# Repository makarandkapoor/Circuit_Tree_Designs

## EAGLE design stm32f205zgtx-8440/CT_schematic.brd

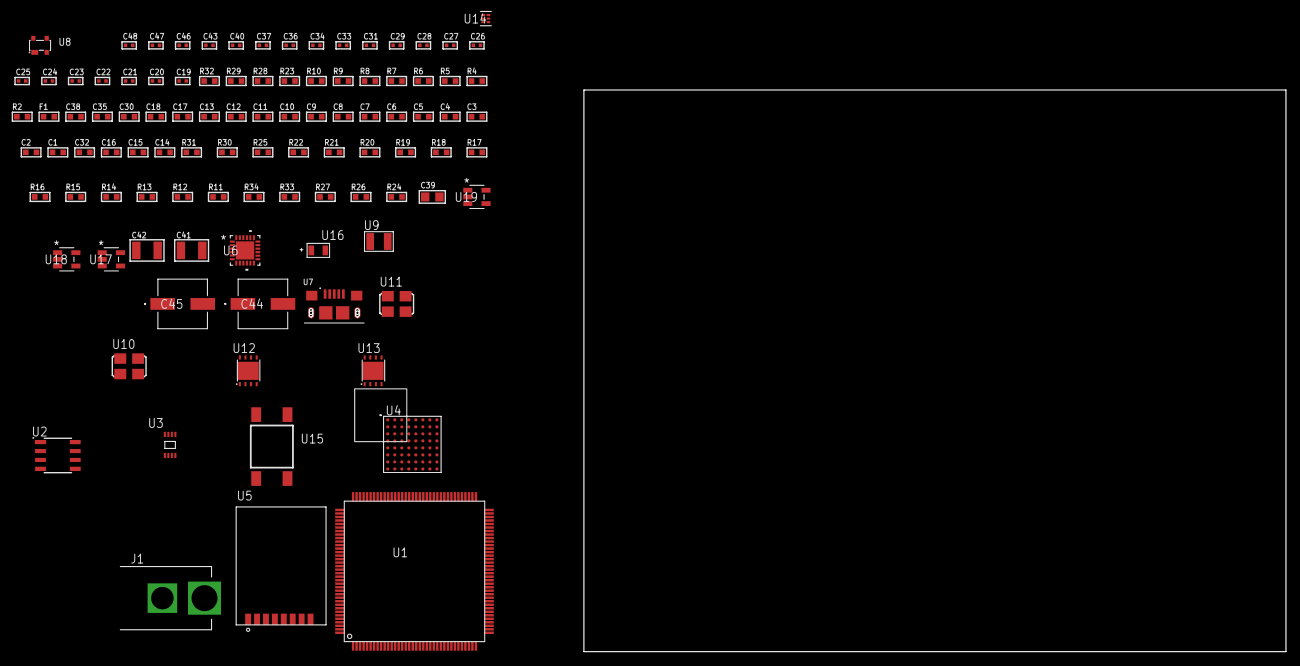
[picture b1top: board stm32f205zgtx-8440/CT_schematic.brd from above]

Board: 2 copper layers, 101 parts (0 on the bottom side), 104 nets, no tracks yet.

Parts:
C1, C18, C30, C35: 1e-06; C0603
C2, C3, C4, C5, C6, C7, C8, C9, C10, C11, C12, C13: 1e-07; C0603
C14: 4.7e-06; C0603
C15, C16, C32: 2.2e-06; C0603
C17: 1e-08; C0603
C19, C20: 1e-11; C0402
C21, C22, C24, C26, C28, C31, C33, C34, C36, C37, C40, C46, C47, C48: 1e-08; C0402
C23, C25, C27, C29, C43: 1e-07; C0402
C38: 8e-07; R0603
C39: 1e-05; C0805
C41, C42: 1e-05; C1210
C44, C45: 0.0001; EXV-9H
F1: 240.0; L0603
J1: PJ-037B; PJ-037B_PACKAGE
R2, R29: 1000.0; R0603
R4, R5, R6: 4700.0; R0603
R7, R8, R9, R10: 2200.0; R0603
R11, R12, R13, R14, R15, R16, R17, R18, R19, R20, R21, R22, R30, R31: 10000.0; R0603
R23: 8060.0; R0603
R24, R26, R27: 100000.0; R0603
R25: 36000.0; R0603
R28: 2231.0; R0603
R32: 9100.0; R0603
R33: 680000.0; R0603
R34: 120000.0; R0603
U1: STM32F205ZGT6; LQFP144
U2: AT24C02D-SSHM-T; AT24C02D
U3: 24AA00T-I/MNY; TDFN-8/6MM
U4: PC28F512P33BFD
U5: RFM75-S
U6: USB3317C-CP-TR; QFN-24
U7: 10118193-0001LF; FCI_10118193-0001LF
U8: prtr5v0u2ax; SOT143B
U9: ABS07-32.768KHZ-7-T
U10: ASFL1-25MHZ-NCS; ASFL1
U11: ASFL1-26MHZ-NCS; ASFL1
U12: LP2951ACSDX/NOPB; WSON-8
U13: LP3878SDX-ADJ/NOPB; WSON-8
U14: TPS3895ADRYR; SON-6
U15: 4-1437565-2; SW_4-1437565-2
U16: Q65110A2395; LGM67K-G1J2-24-Z
U17, U18, U19: nc7sz125m5x; NC7SZ125M5X

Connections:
CLK_CRYSTAL_U1_8: C19.1, U1.8, U9.1
CLK_CRYSTAL_U1_9: C20.1, U1.9, U9.2
CLK_U1_23: U1.23, U10.3
CLK_U6_23: U6.23, U11.3
GND: C1.2, C2.2, C3.2, C4.2, C5.2, C6.2, C7.2, C8.2, C9.2, C10.2, C11.2, C12.2, C13.2, C14.2, C15.2, C16.2, C17.2, C18.2, C19.2, C20.2, C21.2, C22.2, C23.2, C24.2, C25.2, C26.2, C27.2, C28.2, C29.2, C30.2, C31.2, C32.2, C33.2, C34.2, C35.2, C36.2, C37.2, C38.2, C39.2, C40.2, C41.2, C42.2, C43.2, C44.2, C45.2, C46.2, C47.2, C48.2, J1.2, R2.2, R11.2, R12.2, R14.2, R15.2, R23.2, R26.2, R29.2, R32.2, R34.2, U1.16, U1.31, U1.38, U1.51, U1.61, U1.83, U1.94, U1.107, U1.120, U1.130, U2.4, U3.4, U4.B2, U4.H2, U4.H4, U4.H6, U5.1, U6.25, U7.5, U7.6, U7.7, U7.8, U7.9, U8.1, U10.2, U11.2, U12.3, U12.4, U12.PAD, U13.3, U13.PAD, U14.2, U16.C, U17.1, U17.3, U18.1, U18.3, U19.1, U19.3
NET_U1_25: R5.1, U1.25, U18.4
NET_U1_33: C17.1, C18.1, F1.1, U1.32, U1.33
NET_U1_71: C15.1, U1.71
NET_U1_99: R10.1, U1.99, U2.5
NET_U1_100: R9.1, U1.100, U2.6
NET_U1_106: C16.1, U1.106
NET_U1_136: R7.1, U1.136, U3.6
NET_U1_138: R11.1, U1.138
NET_U1_140: R8.1, U1.140, U3.5
NET_U1_142: U15.3, U15.4
NET_U2_1: R13.1, U2.1
NET_U2_2: R14.1, U2.2
NET_U2_3: R15.1, U2.3
NET_U2_7: R12.1, U2.7
NET_U4_A4: C27.1, C28.1, U4.A4
NET_U4_C6: R19.1, U4.C6
NET_U4_D4: R4.1, U4.D4, U17.4
NET_U5_3: R21.1, U5.3
NET_U6_4: C32.1, U6.4
NET_U6_22: R6.1, U6.22, U19.4
NET_U6_24: R23.1, U6.24
NET_U7_1: C35.1, U6.2, U7.1, U8.4
NET_U7_2: U6.5, U7.2, U8.3
NET_U7_3: U6.6, U7.3, U8.2
NET_U12_5: R24.1, U12.5
NET_U12_7: R25.2, R26.1, U12.7
NET_U13_1: C40.1, U13.1
NET_U13_6: R28.2, R29.1, U13.6
NET_U13_8: R27.1, U13.8
NET_U14_1: R31.1, R32.1, U14.1
NET_U14_3: R33.2, R34.1, U14.3
NET_U14_4: R30.1, U14.4, U17.2, U18.2, U19.2
NET_U15_1: R2.1, U15.1, U15.2
PROC_FSMC_A0: U1.10, U4.A1
PROC_FSMC_A1: U1.11, U4.B1
PROC_FSMC_A2: U1.12, U4.C1
PROC_FSMC_A3: U1.13, U4.D1
PROC_FSMC_A4: U1.14, U4.D2
PROC_FSMC_A5: U1.15, U4.A2
PROC_FSMC_A6: U1.50, U4.C2
PROC_FSMC_A7: U1.53, U4.A3
PROC_FSMC_A8: U1.54, U4.B3
PROC_FSMC_A9: U1.55, U4.C3
PROC_FSMC_A10: U1.56, U4.D3
PROC_FSMC_A11: U1.57, U4.C4
PROC_FSMC_A12: U1.87, U4.A5
PROC_FSMC_A13: U1.88, U4.B5
PROC_FSMC_A14: U1.89, U4.C5
PROC_FSMC_A15: U1.90, U4.D7
PROC_FSMC_A16: U1.80, U4.D8
PROC_FSMC_A17: U1.81, U4.A7
PROC_FSMC_A18: U1.82, U4.B7
PROC_FSMC_A19: U1.2, U4.C7
PROC_FSMC_A20: U1.3, U4.C8
PROC_FSMC_A21: U1.4, U4.A8
PROC_FSMC_A22: U1.5, U4.G1
PROC_FSMC_A23: U1.1, U4.H8
PROC_FSMC_A24: U1.128, U4.B6
PROC_FSMC_CLK: U1.117, U4.E6
PROC_FSMC_D0: U1.85, U4.F2
PROC_FSMC_D1: U1.86, U4.E2
PROC_FSMC_D2: U1.114, U4.G3
PROC_FSMC_D3: U1.115, U4.E4
PROC_FSMC_D4: U1.58, U4.E5
PROC_FSMC_D5: U1.59, U4.G5
PROC_FSMC_D6: U1.60, U4.G6
PROC_FSMC_D7: U1.63, U4.H7
PROC_FSMC_D8: U1.64, U4.E1
PROC_FSMC_D9: U1.65, U4.E3
PROC_FSMC_D10: U1.66, U4.F3
PROC_FSMC_D11: U1.67, U4.F4
PROC_FSMC_D12: U1.68, U4.F5
PROC_FSMC_D13: U1.77, U4.H5
PROC_FSMC_D14: U1.78, U4.G7
PROC_FSMC_D15: U1.79, U4.E7
PROC_FSMC_NE1: R17.1, U1.123, U4.B4
PROC_FSMC_NL: R16.1, U1.137, U4.F6
PROC_FSMC_NOE: R18.1, U1.118, U4.F8
PROC_FSMC_NWAIT: U1.122, U4.F7
PROC_FSMC_NWE: R20.1, U1.119, U4.G8
PROC_SPI1_MISO: U1.42, U5.7
PROC_SPI1_MOSI: U1.43, U5.6
PROC_SPI1_NSS: R22.1, U1.40, U5.4
PROC_SPI1_SCK: U1.133, U5.5
PROC_USB_OTG_HS_ULPI_CK: U1.41, U6.12
PROC_USB_OTG_HS_ULPI_D0: U1.37, U6.16
PROC_USB_OTG_HS_ULPI_D1: U1.46, U6.15
PROC_USB_OTG_HS_ULPI_D2: U1.47, U6.14
PROC_USB_OTG_HS_ULPI_D3: U1.69, U6.13
PROC_USB_OTG_HS_ULPI_D4: U1.70, U6.11
PROC_USB_OTG_HS_ULPI_D5: U1.73, U6.10
PROC_USB_OTG_HS_ULPI_D6: U1.74, U6.9
PROC_USB_OTG_HS_ULPI_D7: U1.135, U6.8
PROC_USB_OTG_HS_ULPI_DIR: U1.28, U6.19
PROC_USB_OTG_HS_ULPI_NXT: U1.29, U6.18
PROC_USB_OTG_HS_ULPI_STP: U1.26, U6.20
VCC_S1_11V4: C38.1, C41.1, C44.1, C45.1, J1.1, R27.2, U12.8, U13.4
VCC_TIER1_1V8: C34.1, C39.1, C46.1, C47.1, C48.1, R24.2, R25.1, U6.21, U12.1, U17.5, U18.5, U19.5
VCC_TIER1_3V3: C1.1, C2.1, C3.1, C4.1, C5.1, C6.1, C7.1, C8.1, C9.1, C10.1, C11.1, C12.1, C13.1, C14.1, C21.1, C22.1, C23.1, C24.1, C25.1, C26.1, C29.1, C30.1, C31.1, C33.1, C36.1, C37.1, C42.1, C43.1, F1.2, R4.2, R5.2, R6.2, R7.2, R8.2, R9.2, R10.2, R13.2, R16.2, R17.2, R18.2, R19.2, R20.2, R21.2, R22.2, R28.1, R30.2, R31.2, R33.1, U1.6, U1.17, U1.30, U1.39, U1.52, U1.62, U1.72, U1.84, U1.95, U1.108, U1.121, U1.131, U1.144, U2.8, U3.8, U4.A6, U4.D5, U4.D6, U4.G4, U4.H3, U5.2, U6.3, U6.17, U10.4, U11.4, U13.5, U14.6

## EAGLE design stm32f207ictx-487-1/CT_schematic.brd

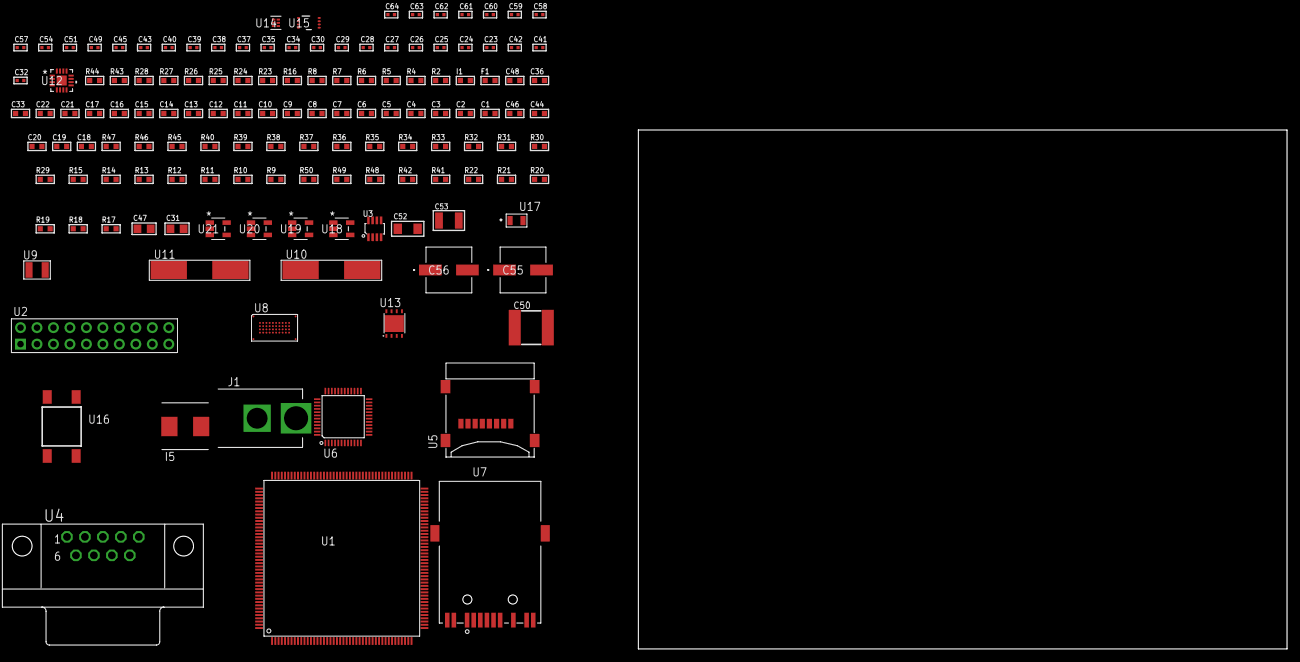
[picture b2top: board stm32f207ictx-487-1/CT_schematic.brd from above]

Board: 2 copper layers, 100.0 x 80.0 mm, 137 parts (0 on the bottom side), 100 nets, no tracks yet.

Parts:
C1, C22, C33, C36, C48: 1e-06; C0603
C2, C3, C4, C5, C6, C7, C8, C9, C10, C11, C12, C13, C14, C15, C16, C17: 1e-07; C0603
C18: 4.7e-06; C0603
C19, C20, C44, C46: 2.2e-06; C0603
C21: 1e-08; C0603
C23, C24, C25, C26: 1e-11; C0402
C27, C28, C29, C30, C34, C37, C39, C40, C43, C45, C49, C54, C58, C60: 1e-07; C0402
C31, C47: 1e-05; C0805
C32: 2.2e-08; C0402
C35, C38, C51, C57, C59, C61, C62, C63, C64: 1e-08; C0402
C41, C42: 2.7e-11; C0402
C50: 6.8e-05; 2220
C52: 1e-05; C1206
C53: 1e-05; C1210
C55, C56: 0.0001; EXV-9H
F1: 240.0; L0603
I1: 97.0; R0603
I5: 3.3e-06; WE-HCI_7030/7040/7050
J1: PJ-037B; PJ-037B_PACKAGE
R2, R44: 1000.0; R0603
R4, R5, R6, R28: 4700.0; R0603
R7, R8: 2200.0; R0603
R9, R10, R11, R12, R13, R14, R15, R29, R30, R31, R32, R33, R34, R35, R36, R37, R38, R45, R46: 10000.0; R0603
R16: 120.0; R0603
R17, R18, R19, R20, R21, R22, R42: 100000.0; R0603
R23, R24: 0.1; R0603
R25, R26: 200.0; R0603
R27: 2490.0; R0603
R39: 20000.0; R0603
R40: 39000.0; R0603
R41, R48: 300000.0; R0603
R43: 2231.0; R0603
R47: 82000.0; R0603
R49: 120000.0; R0603
R50: 200000.0; R0603
U1: STM32F207ICT6; LQFP176
U2: TST-110-05-T-D-RA
U3: MAX3051EKA+T; SOT-23-8
U4: 182-009-113R531; 182-009-MALE
U5: 0472192001; MOLEX_47219-2001
U6: RTL8201FL-VB-CG
U7: 7498011122R
U8: S29VS256RABBHW000
U9: ABS07-32.768KHZ-7-T
U10, U11: ABLS-25.000MHZ-B2F-T
U12: LTC3601EUD#PBF; QFN-16_EP
U13: LP3878SDX-ADJ/NOPB; WSON-8
U14: TPS3895ADRYR; SON-6
U15: LSF0102DCTR; DCU0008A_N
U16: 4-1437565-2; SW_4-1437565-2
U17: Q65110A2395; LGM67K-G1J2-24-Z
U18, U19, U20, U21: nc7sz125m5x; NC7SZ125M5X

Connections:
CLK_CRYSTAL_U1_9: C23.1, U1.9, U9.1
CLK_CRYSTAL_U1_10: C24.1, U1.10, U9.2
CLK_CRYSTAL_U1_29: C25.1, U1.29, U10.1
CLK_CRYSTAL_U1_30: C26.1, U1.30, U10.2
CLK_CRYSTAL_U6_42: C42.1, U6.42, U11.1
CLK_CRYSTAL_U6_43: C41.1, U6.43, U11.2
GND: C1.2, C2.2, C3.2, C4.2, C5.2, C6.2, C7.2, C8.2, C9.2, C10.2, C11.2, C12.2, C13.2, C14.2, C15.2, C16.2, C17.2, C18.2, C19.2, C20.2, C21.2, C22.2, C23.2, C24.2, C25.2, C26.2, C27.2, C28.2, C29.2, C30.2, C31.2, C32.2, C33.2, C34.2, C35.2, C36.2, C37.2, C38.2, C39.2, C40.2, C41.2, C42.2, C43.2, C44.2, C45.2, C46.2, C47.2, C48.2, C50.1, C50.2, C51.2, C52.2, C53.2, C54.2, C55.2, C56.2, C57.2, C58.2, C59.2, C60.2, C61.2, C62.2, C63.2, C64.2, J1.2, R2.2, R9.2, R15.2, R23.2, R24.2, R27.2, R29.2, R32.2, R39.2, R41.2, R44.2, R47.2, R49.2, U1.14, U1.22, U1.37, U1.48, U1.61, U1.71, U1.90, U1.102, U1.113, U1.126, U1.135, U1.148, U1.158, U2.4, U2.6, U2.8, U2.10, U2.12, U2.14, U2.16, U2.18, U2.20, U3.2, U3.8, U4.5, U5.6, U5.G1, U5.G2, U5.G3, U5.G4, U6.7, U6.20, U6.33, U6.47, U8.C5, U8.D12, U8.E3, U8.F5, U12.1, U12.9, U12.17, U13.3, U13.PAD, U14.2, U15.1, U17.C, U18.2, U18.3, U19.1, U19.3, U20.1, U20.3, U21.1, U21.3
NET_U1_31: R6.1, U1.31, U21.4
NET_U1_39: C21.1, C22.1, F1.1, U1.38, U1.39
NET_U1_81: C19.1, U1.81
NET_U1_125: C20.1, U1.125
NET_U1_166: R9.1, U1.166
NET_U1_176: U16.3, U16.4
NET_U2_19: R15.1, U2.19
NET_U3_6: R16.2, U3.6
NET_U4_2: R16.2, U3.6, U4.2
NET_U4_3: R16.1, U3.7, U4.3
NET_U6_6: C33.1, C34.1, C35.1, I1.1, U6.6, U6.41
NET_U6_10: R32.1, U6.10
NET_U6_13: R29.1, U6.13
NET_U6_18: R33.1, U6.18
NET_U6_29: R4.1, U6.29, U19.4
NET_U6_32: R28.1, U6.32
NET_U6_34: R30.1, U6.34
NET_U6_35: R31.1, U6.35
NET_U6_39: R34.1, U6.39
NET_U6_40: C40.1, U6.40
NET_U6_46: R27.1, U6.46
NET_U6_48: C39.1, U6.48
NET_U7_1: U6.1, U7.1
NET_U7_3: U6.2, U7.3
NET_U7_4: U6.4, U7.4
NET_U7_5: C32.1, U7.2, U7.5
NET_U7_6: U6.5, U7.6
NET_U7_8: R24.1, U7.8
NET_U7_10: R25.1, U7.10
NET_U7_12: R26.1, U7.12
NET_U7_13: R23.1, U7.13, U7.14
NET_U8_D8: R5.1, U8.D8, U20.4
NET_U12_3: C49.2, I5.1, U12.3, U12.4
NET_U12_6: C49.1, U12.6
NET_U12_7: C48.1, U12.7, U12.12
NET_U12_10: R41.1, U12.10
NET_U12_11: R39.1, R40.1, U12.11
NET_U12_ATNET_3: I5.2, R40.2
NET_U13_1: C51.1, U13.1
NET_U13_6: R43.2, R44.1, U13.6
NET_U13_8: R42.1, U13.8
NET_U14_1: R46.1, R47.1, U14.1
NET_U14_3: R48.2, R49.1, U14.3
NET_U14_4: R45.1, U14.4, U18.4, U19.2, U20.2, U21.2
NET_U15_8: R50.1, U15.8
NET_U16_1: R2.1, U16.1, U16.2
PROC_CAN1_RX_TOXCVR: U3.4, U15.5
PROC_CAN1_TX_TOXCVR: U3.1, U15.6
PROC_FSMC_A16: U1.99, U8.D4
PROC_FSMC_A17: U1.100, U8.C11
PROC_FSMC_A18: U1.101, U8.D10
PROC_FSMC_A19: U1.2, U8.C10
PROC_FSMC_A20: U1.3, U8.D5
PROC_FSMC_A21: U1.4, U8.C4
PROC_FSMC_A22: U1.5, U8.C12
PROC_FSMC_A23: U1.1, U8.D7
PROC_FSMC_CLK: U1.145, U8.C6
PROC_FSMC_D0: U1.104, U8.F3
PROC_FSMC_D1: U1.105, U8.F4
PROC_FSMC_D2: U1.142, U8.E6
PROC_FSMC_D3: U1.143, U8.E7
PROC_FSMC_D4: U1.68, U8.F8
PROC_FSMC_D5: U1.69, U8.F9
PROC_FSMC_D6: U1.70, U8.E10
PROC_FSMC_D7: U1.73, U8.E11
PROC_FSMC_D8: U1.74, U8.E4
PROC_FSMC_D9: U1.75, U8.E5
PROC_FSMC_D10: U1.76, U8.F6
PROC_FSMC_D11: U1.77, U8.F7
PROC_FSMC_D12: U1.78, U8.E8
PROC_FSMC_D13: U1.96, U8.E9
PROC_FSMC_D14: U1.97, U8.F11
PROC_FSMC_D15: U1.98, U8.F12
PROC_FSMC_NE1: R36.1, U1.151, U8.D11
PROC_FSMC_NL: U1.165, U8.D6
PROC_FSMC_NOE: R38.1, U1.146, U8.E12
PROC_FSMC_NWAIT: R35.1, U1.150, U8.C3
PROC_FSMC_NWE: R37.1, U1.147, U8.C8
PROC_SDIO_CK: R18.1, U1.141, U5.5
PROC_SDIO_CMD: R17.1, U1.144, U5.3
PROC_SDIO_D0: R19.1, U1.117, U5.7
PROC_SDIO_D1: R20.1, U1.118, U5.8
PROC_SDIO_D2: R21.1, U1.139, U5.1
PROC_SDIO_D3: R22.1, U1.140, U5.2
PROC_SYS_JTDI: R11.1, U1.138, U2.5
PROC_SYS_JTDO_SWO: U1.161, U2.13
PROC_SYS_JTMS_SWDIO: R12.1, U1.124, U2.7
PROC_SYS_JTRST: R10.1, U1.162, U2.3
PROC_SYS_TRACECLK: R13.1, U1.137, U2.9
RST_OUT_U2_SRESET_B: R14.1, U2.15, U18.1
VCC_S1_8V9: C47.1, C52.1, C55.1, C56.1, J1.1, R42.2, U12.15, U12.16, U13.4
VCC_TIER1_1V8: C1.1, C2.1, C3.1, C4.1, C5.1, C6.1, C7.1, C8.1, C9.1, C10.1, C11.1, C12.1, C13.1, C14.1, C15.1, C16.1, C17.1, C18.1, C28.1, C30.1, C31.1, C43.1, C44.1, C45.1, C46.1, C50.2, C54.1, C59.1, C60.1, C61.1, C62.1, C63.1, C64.1, F1.2, I5.2, R5.2, R6.2, R7.2, R8.2, R10.2, R11.2, R12.2, R13.2, R14.2, R17.2, R18.2, R19.2, R20.2, R21.2, R22.2, R35.2, R36.2, R37.2, R38.2, R40.2, R45.2, R46.2, R48.1, U1.6, U1.15, U1.23, U1.36, U1.49, U1.62, U1.72, U1.82, U1.91, U1.103, U1.114, U1.127, U1.136, U1.149, U1.159, U1.172, U2.1, U5.4, U8.C7, U8.D3, U8.F10, U12.8, U14.6, U15.2, U18.5, U19.5, U20.5, U21.5
VCC_TIER1_3V3: C27.1, C29.1, C36.1, C37.1, C38.1, C53.1, C57.1, C58.1, I1.2, R4.2, R28.2, R30.2, R31.2, R33.2, R34.2, R43.1, R50.2, U2.2, U3.3, U6.15, U6.21, U6.37, U7.9, U7.11, U13.5, U15.7

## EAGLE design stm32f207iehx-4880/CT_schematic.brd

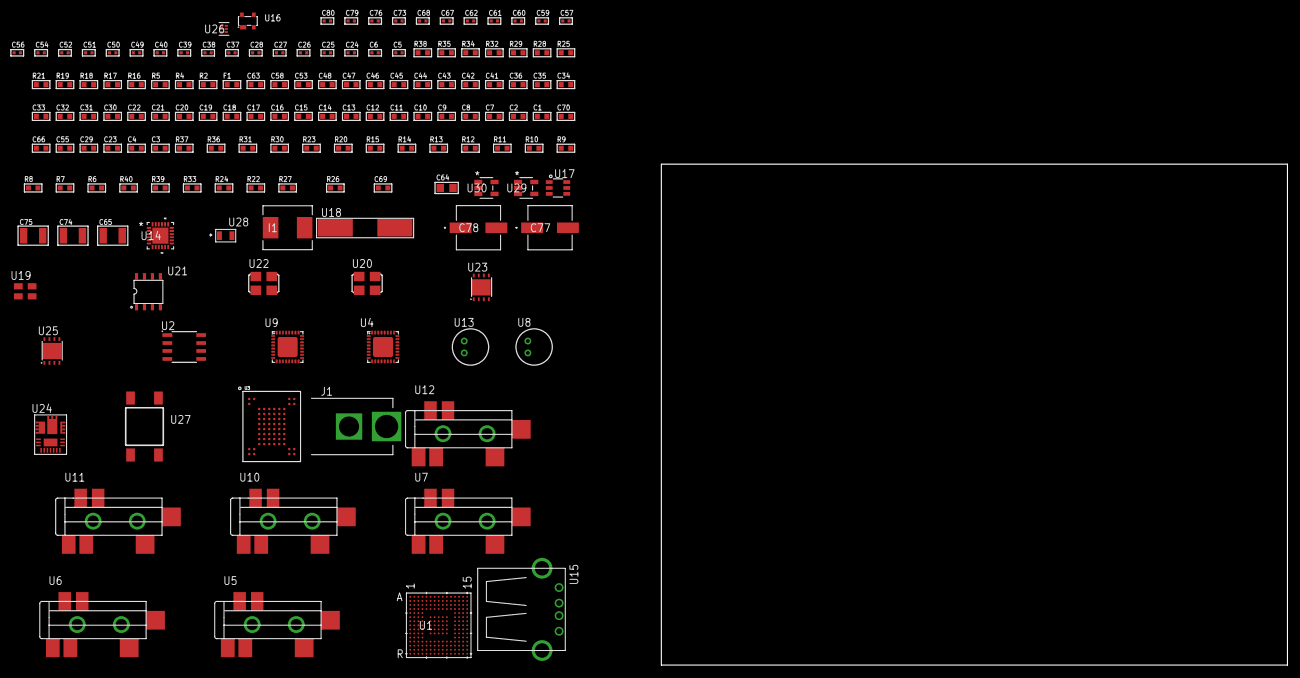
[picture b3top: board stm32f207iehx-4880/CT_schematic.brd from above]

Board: 2 copper layers, 100.0 x 80.0 mm, 149 parts (0 on the bottom side), 111 nets, no tracks yet.

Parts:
C1: 1e-08; C0603
C2, C7, C30, C31, C32, C33, C34, C35, C36, C41, C42, C43, C44, C45, C46, C47, C48, C53: 1e-06; C0603
C3, C4, C29, C55, C66: 2.2e-06; C0603
C5, C6: 1e-11; C0402
C8, C9, C10, C11, C12, C13, C14, C15, C16, C17, C18, C19, C20, C21, C22: 1e-07; C0603
C23: 4.7e-06; C0603
C24, C54, C56, C57, C59, C60, C61, C62, C73, C79, C80: 1e-08; C0402
C25, C26, C27, C28, C37, C38, C39, C40, C49, C50, C51, C52, C67, C68, C76: 1e-07; C0402
C58: 0.0001; R0603
C63: 8e-07; R0603
C64: 1e-05; C0805
C65: 0.0001; C1210
C69: 7.7470032193169e-09; R0603
C70: 2.7e-07; C0603
C74, C75: 1e-05; C1210
C77, C78: 0.0001; EXV-9H
F1: 240.0; L0603
I1: 6.8e-07; IND25X25CZ
J1: PJ-037B; PJ-037B_PACKAGE
R2, R35: 1000.0; R0603
R4, R5: 4700.0; R0603
R6, R7, R8, R9, R10, R11, R12, R13, R14, R15, R36, R37: 10000.0; R0603
R16, R17, R18, R19: 1270.0; R0603
R20: 47000.0; R0603
R21: 8060.0; R0603
R22, R24, R33: 100000.0; R0603
R23: 36000.0; R0603
R25: 0.1; R0603
R26: 4030.2416170974; R0603
R27: 719.68600305311; R0603
R28: 68.0; R0603
R29: 130.0; R0603
R30: 39000.0; R0603
R31: 49900.0; R0603
R32: 5600.0; R0603
R34: 3900.0; R0603
R38: 9100.0; R0603
R39: 680000.0; R0603
R40: 120000.0; R0603
U1: STM32F207IEH6; UFBGA176_25
U2: AT25160B-SSHL-T; SOIC-8
U3: mt29f4g08abadah4; VFBGA-63
U4, U9: SGTL5000XNAA3; QFN-32
U5, U6, U7, U10, U11, U12: SJ-43515TS-SMT-TR
U8, U13: WM-64PCT; WM-64PC
U14: USB3317C-CP-TR; QFN-24
U15: 61400416021; USB-A-H
U16: prtr5v0u2ax; SOT143B
U17: MAX4995AAUT+T; SOT-23-6
U18: ABLS-25.000MHZ-B2F-T
U19: ASEK-32.768KHz-ECST; ASEK
U20: ASFL-24.57MHZ-NCS; ASFL1
U21: idt74fct38072; IDT74FCT38072
U22: ASFL1-26MHZ-NCS; ASFL1
U23: LP2951ACSDX/NOPB; WSON-8
U24: IR3899MTR1PBF
U25: LP3878SDX-ADJ/NOPB; WSON-8
U26: TPS3895ADRYR; SON-6
U27: 4-1437565-2; SW_4-1437565-2
U28: Q65110A2395; LGM67K-G1J2-24-Z
U29, U30: nc7sz125m5x; NC7SZ125M5X

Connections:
CLK_CRYSTAL_U1_G1: C5.1, U1.G1, U18.1
CLK_CRYSTAL_U1_H1: C6.1, U1.H1, U18.2
CLK_U1_E1: U1.E1, U19.3
CLK_U4_21: U4.21, U21.7
CLK_U9_21: U9.21, U21.6
CLK_U14_23: U14.23, U22.3
CLK_U21_3: U20.3, U21.3
GND: C1.2, C2.2, C3.2, C4.2, C5.2, C6.2, C7.2, C8.2, C9.2, C10.2, C11.2, C12.2, C13.2, C14.2, C15.2, C16.2, C17.2, C18.2, C19.2, C20.2, C21.2, C22.2, C23.2, C24.2, C25.2, C26.2, C27.2, C28.2, C29.2, C37.2, C38.2, C39.2, C40.2, C41.2, C49.2, C50.2, C51.2, C52.2, C53.2, C54.2, C55.2, C56.2, C57.2, C58.2, C59.2, C60.2, C61.2, C62.2, C63.2, C64.2, C66.2, C67.2, C68.2, C73.2, C74.2, C75.2, C76.2, C77.2, C78.2, C79.2, C80.2, J1.2, R2.2, R6.2, R7.2, R17.2, R19.2, R20.2, R21.2, R24.2, R25.1, R25.2, R27.2, R30.2, R32.2, R35.2, R38.2, R40.2, U1.D5, U1.D7, U1.D8, U1.D9, U1.F2, U1.F6, U1.F7, U1.F8, U1.F9, U1.F10, U1.F12, U1.G2, U1.G6, U1.G7, U1.G8, U1.G9, U1.G10, U1.G12, U1.H6, U1.H7, U1.H8, U1.H9, U1.H10, U1.H12, U1.J6, U1.J7, U1.J8, U1.J9, U1.J10, U1.K6, U1.K7, U1.K8, U1.K9, U1.K10, U1.M1, U1.M8, U1.M9, U1.N1, U2.4, U3.C5, U3.F7, U3.K3, U3.K8, U4.1, U4.3, U4.7, U4.EXP, U6.1, U7.1, U8.2, U9.1, U9.3, U9.7, U9.EXP, U11.1, U12.1, U13.2, U14.1, U14.25, U15.4, U15.5, U15.6, U16.1, U17.2, U19.2, U20.2, U21.4, U21.5, U21.8, U22.2, U23.3, U23.4, U23.PAD, U24.4, U24.11, U24.17, U25.3, U25.PAD, U26.2, U28.C, U29.1, U29.3, U30.1, U30.3
NET_U1_D6: R6.1, U1.D6
NET_U1_F13: C4.1, U1.F13
NET_U1_J1: R4.1, U1.J1, U29.4
NET_U1_L4: R7.1, U1.L4
NET_U1_M10: C3.1, U1.M10
NET_U1_R1: C1.1, C2.1, F1.1, U1.P1, U1.R1
NET_U1_R15: U27.3, U27.4
NET_U2_3: R8.1, U2.3
NET_U2_7: R10.1, U2.7
NET_U3_C3: R15.1, U3.C3
NET_U4_10: C40.1, U4.10
NET_U4_29: R16.1, U4.29
NET_U4_31: R17.1, U4.31
NET_U5_1: U4.4, U5.1
NET_U5_2: U4.2, U5.2
NET_U5_5: U4.6, U5.5
NET_U6_2: C31.1, U6.2
NET_U6_5: C30.1, U6.5
NET_U7_2: C33.1, C34.1, U7.2
NET_U7_5: C32.1, U7.5
NET_U7_13: C33.2, C34.2
NET_U8_1: C35.1, C36.1, C41.1, U4.16, U8.1
NET_U8_15: C35.2, C36.2
NET_U9_10: C52.1, U9.10
NET_U9_29: R18.1, U9.29
NET_U9_31: R19.1, U9.31
NET_U10_1: U9.4, U10.1
NET_U10_2: U9.2, U10.2
NET_U10_5: U9.6, U10.5
NET_U11_2: C43.1, U11.2
NET_U11_5: C42.1, U11.5
NET_U12_2: C45.1, C46.1, U12.2
NET_U12_5: C44.1, U12.5
NET_U12_13: C45.2, C46.2
NET_U13_1: C47.1, C48.1, C53.1, U9.16, U13.1
NET_U13_15: C47.2, C48.2
NET_U14_4: C55.1, U14.4
NET_U14_22: R5.1, U14.22, U30.4
NET_U14_24: R21.1, U14.24
NET_U15_1: C58.1, U14.2, U15.1, U16.4, U17.1
NET_U15_2: U14.5, U15.2, U16.3
NET_U15_3: U14.6, U15.3, U16.2
NET_U17_3: R20.1, U17.3
NET_U17_4: U14.7, U17.4
NET_U23_5: R22.1, U23.5
NET_U23_7: R23.2, R24.1, U23.7
NET_U24_1: C69.1, R26.1, R27.1, R28.1, R29.1, U24.1, U24.8
NET_U24_2: C68.1, U24.2
NET_U24_3: C69.2, C70.1, C70.2, U24.3
NET_U24_5: R30.1, U24.5
NET_U24_10: C66.1, U24.10
NET_U24_12: C65.1, I1.1, U24.12
NET_U24_14: C65.2, U24.14
NET_U24_15: R31.1, R32.1, U24.15
NET_U24_ATNET_3: I1.2, R26.2
NET_U24_ATNET_4: C70.2, R28.2
NET_U25_1: C73.1, U25.1
NET_U25_6: R34.2, R35.1, U25.6
NET_U25_8: R33.1, U25.8
NET_U26_1: R37.1, R38.1, U26.1
NET_U26_3: R39.2, R40.1, U26.3
NET_U26_4: R36.1, U26.4, U29.2, U30.2
NET_U27_1: R2.1, U27.1, U27.2
PROC_FSMC_A16: U1.N14, U3.D5
PROC_FSMC_A17: U1.N13, U3.C4
PROC_FSMC_D0: U1.M14, U3.H4
PROC_FSMC_D1: U1.L14, U3.J4
PROC_FSMC_D2: U1.B12, U3.K4
PROC_FSMC_D3: U1.C12, U3.K5
PROC_FSMC_D4: U1.R8, U3.K6
PROC_FSMC_D5: U1.P8, U3.J7
PROC_FSMC_D6: U1.P9, U3.K7
PROC_FSMC_D7: U1.R9, U3.J8
PROC_FSMC_INT3: R11.1, U1.J14, U3.C8
PROC_FSMC_NCE2: R12.1, U1.A11, U3.C6
PROC_FSMC_NOE: R14.1, U1.D10, U3.D4
PROC_FSMC_NWE: R13.1, U1.C11, U3.C7
PROC_I2S2_SCK: U1.D14, U4.24
PROC_I2S2_SD: U1.C13, U4.26
PROC_I2S2_WS: U1.B4, U4.23
PROC_I2S3_SCK: U1.B14, U9.24
PROC_I2S3_SD: U1.A12, U9.26
PROC_I2S3_WS: U1.A13, U9.23
PROC_SPI1_MISO: U1.A9, U2.2
PROC_SPI1_MOSI: U1.R3, U2.5
PROC_SPI1_NSS: R9.1, U1.N4, U2.1
PROC_SPI1_SCK: U1.A10, U2.6
PROC_USB_OTG_HS_ULPI_CK: U1.P4, U14.12
PROC_USB_OTG_HS_ULPI_D0: U1.R2, U14.16
PROC_USB_OTG_HS_ULPI_D1: U1.R5, U14.15
PROC_USB_OTG_HS_ULPI_D2: U1.R4, U14.14
PROC_USB_OTG_HS_ULPI_D3: U1.R12, U14.13
PROC_USB_OTG_HS_ULPI_D4: U1.R13, U14.11
PROC_USB_OTG_HS_ULPI_D5: U1.P12, U14.10
PROC_USB_OTG_HS_ULPI_D6: U1.P13, U14.9
PROC_USB_OTG_HS_ULPI_D7: U1.A6, U14.8
PROC_USB_OTG_HS_ULPI_DIR: U1.E4, U14.19
PROC_USB_OTG_HS_ULPI_NXT: U1.H4, U14.18
PROC_USB_OTG_HS_ULPI_STP: U1.M2, U14.20
VCC_S1_15V9: C63.1, C67.1, C74.1, C77.1, C78.1, J1.1, R31.2, R33.2, U23.8, U24.9, U25.4
VCC_TIER1_1V8: C37.1, C38.1, C49.1, C50.1, C57.1, C64.1, C79.1, C80.1, R22.2, R23.1, U4.5, U4.30, U9.5, U9.30, U14.21, U23.1, U29.5, U30.5
VCC_TIER1_3V3: C7.1, C8.1, C9.1, C10.1, C11.1, C12.1, C13.1, C14.1, C15.1, C16.1, C17.1, C18.1, C19.1, C20.1, C21.1, C22.1, C23.1, C24.1, C25.1, C26.1, C27.1, C28.1, C29.1, C39.1, C51.1, C54.1, C56.1, C59.1, C60.1, C61.1, C62.1, C76.1, F1.2, I1.2, R4.2, R5.2, R8.2, R9.2, R10.2, R11.2, R12.2, R13.2, R14.2, R15.2, R16.2, R18.2, R26.2, R36.2, R37.2, R39.1, U1.C1, U1.C5, U1.C7, U1.C8, U1.C9, U1.F3, U1.G3, U1.G13, U1.H13, U1.J12, U1.J13, U1.K4, U1.N8, U1.N9, U1.N10, U2.8, U3.D3, U3.G4, U3.H8, U3.J6, U4.20, U9.20, U14.3, U14.17, U19.4, U20.4, U21.1, U21.2, U22.4, U26.6
VCC_TIER1_5V0: C75.1, R34.1, U17.5, U25.5

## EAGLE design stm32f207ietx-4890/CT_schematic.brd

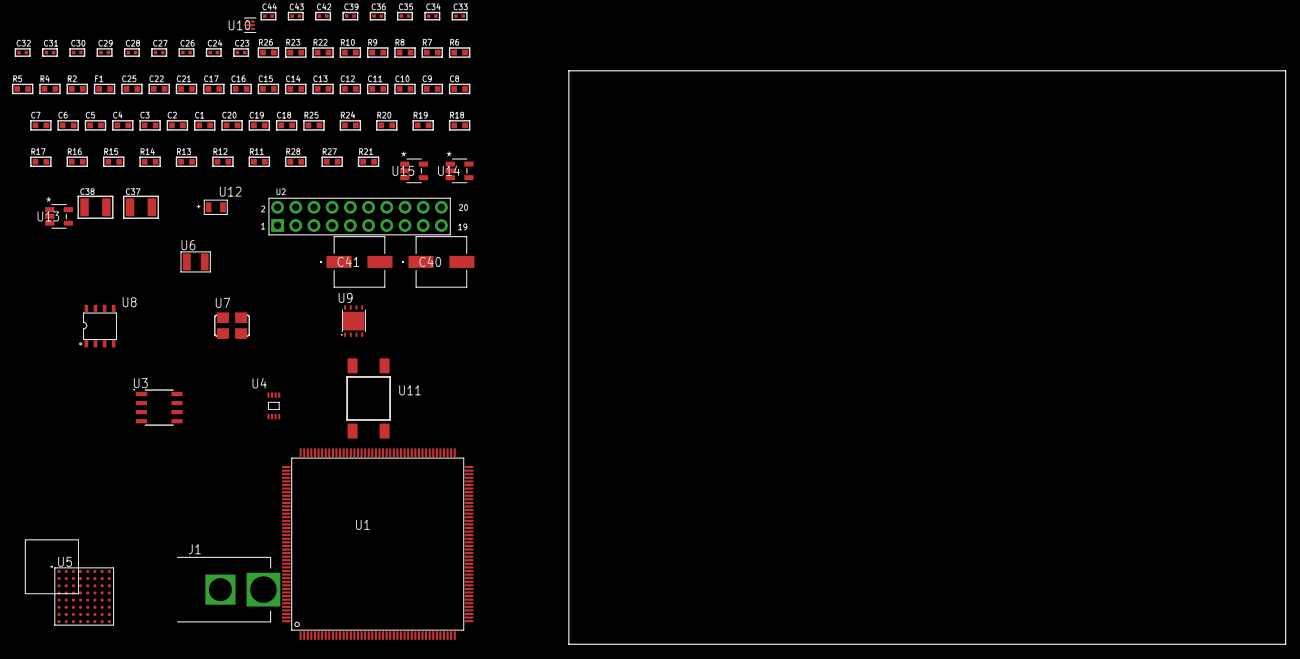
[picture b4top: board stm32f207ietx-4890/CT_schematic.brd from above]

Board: 2 copper layers, 100.0 x 80.0 mm, 87 parts (0 on the bottom side), 71 nets, no tracks yet.

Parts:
C1, C22, C25: 1e-06; C0603
C2, C3, C4, C5, C6, C7, C8, C9, C10, C11, C12, C13, C14, C15, C16, C17: 1e-07; C0603
C18: 4.7e-06; C0603
C19, C20: 2.2e-06; C0603
C21: 1e-08; C0603
C23, C24: 1e-11; C0402
C26, C27, C29, C31, C33, C34, C35, C36, C42, C43, C44: 1e-08; C0402
C28, C30, C32, C39: 1e-07; C0402
C37, C38: 1e-05; C1210
C40, C41: 0.0001; EXV-9H
F1: 240.0; L0603
J1: PJ-037B; PJ-037B_PACKAGE
R2, R23: 1000.0; R0603
R4, R5, R6: 4700.0; R0603
R7, R8, R9, R10: 2200.0; R0603
R11, R12, R13, R14, R15, R16, R17, R18, R19, R20, R24, R25: 10000.0; R0603
R21: 100000.0; R0603
R22: 2231.0; R0603
R26: 9100.0; R0603
R27: 680000.0; R0603
R28: 120000.0; R0603
U1: STM32F207IET6; LQFP176
U2: arducam_ov2640; ARDUCAM
U3: AT24C02D-SSHM-T; AT24C02D
U4: 24AA16-I/MC; TDFN-8/6MM
U5: PC28F512P33BFD
U6: ABS07-32.768KHZ-7-T
U7: ASFL1-25MHZ-NCS; ASFL1
U8: idt74fct38072; IDT74FCT38072
U9: LP3878SDX-ADJ/NOPB; WSON-8
U10: TPS3895ADRYR; SON-6
U11: 4-1437565-2; SW_4-1437565-2
U12: Q65110A2395; LGM67K-G1J2-24-Z
U13, U14, U15: nc7sz125m5x; NC7SZ125M5X

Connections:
CLK_CRYSTAL_U1_9: C23.1, U1.9, U6.1
CLK_CRYSTAL_U1_10: C24.1, U1.10, U6.2
CLK_U1_29: U1.29, U8.6
CLK_U2_8: U2.8, U8.7
CLK_U8_3: U7.3, U8.3
GND: C1.2, C2.2, C3.2, C4.2, C5.2, C6.2, C7.2, C8.2, C9.2, C10.2, C11.2, C12.2, C13.2, C14.2, C15.2, C16.2, C17.2, C18.2, C19.2, C20.2, C21.2, C22.2, C23.2, C24.2, C25.2, C26.2, C27.2, C28.2, C29.2, C30.2, C31.2, C32.2, C33.2, C34.2, C35.2, C36.2, C37.2, C38.2, C39.2, C40.2, C41.2, C42.2, C43.2, C44.2, J1.2, R2.2, R11.2, R12.2, R14.2, R15.2, R23.2, R26.2, R28.2, U1.14, U1.22, U1.37, U1.48, U1.61, U1.71, U1.90, U1.102, U1.113, U1.126, U1.135, U1.148, U1.158, U2.2, U2.20, U3.4, U4.4, U4.7, U5.B2, U5.H2, U5.H4, U5.H6, U7.2, U8.4, U8.5, U8.8, U9.3, U9.PAD, U10.2, U12.C, U13.1, U13.3, U14.1, U14.3, U15.1, U15.3
NET_U1_31: R5.1, U1.31, U14.4
NET_U1_39: C21.1, C22.1, F1.1, U1.38, U1.39
NET_U1_45: R9.1, U1.45, U4.6
NET_U1_46: R10.1, U1.46, U4.5
NET_U1_81: C19.1, U1.81
NET_U1_125: C20.1, U1.125
NET_U1_164: R7.1, U1.164, U3.6
NET_U1_166: R11.1, U1.166
NET_U1_168: R8.1, U1.168, U3.5
NET_U1_175: U11.3, U11.4
NET_U2_19: R6.1, U2.19, U15.4
NET_U3_1: R13.1, U3.1
NET_U3_2: R14.1, U3.2
NET_U3_3: R15.1, U3.3
NET_U3_7: R12.1, U3.7
NET_U5_A4: C32.1, C33.1, U5.A4
NET_U5_C6: R19.1, U5.C6
NET_U5_D4: R4.1, U5.D4, U13.4
NET_U9_1: C36.1, U9.1
NET_U9_6: R22.2, R23.1, U9.6
NET_U9_8: R21.1, U9.8
NET_U10_1: R25.1, R26.1, U10.1
NET_U10_3: R27.2, R28.1, U10.3
NET_U10_4: R24.1, U10.4, U13.2, U14.2, U15.2
NET_U11_1: R2.1, U11.1, U11.2
PROC_DCMI_D0: U1.86, U2.18
PROC_DCMI_D1: U1.87, U2.17
PROC_DCMI_D2: U1.88, U2.16
PROC_DCMI_D3: U1.89, U2.15
PROC_DCMI_D4: U1.129, U2.14
PROC_DCMI_D5: U1.173, U2.13
PROC_DCMI_D6: U1.167, U2.12
PROC_DCMI_D7: U1.176, U2.11
PROC_DCMI_D8: U1.132, U2.10
PROC_DCMI_D9: U1.133, U2.9
PROC_DCMI_HSYNC: U1.50, U2.6
PROC_DCMI_PIXCK: U1.52, U2.7
PROC_DCMI_VSYNC: U1.174, U2.5
PROC_FSMC_A0: U1.16, U5.A1
PROC_FSMC_A1: U1.17, U5.B1
PROC_FSMC_A2: U1.18, U5.C1
PROC_FSMC_A3: U1.19, U5.D1
PROC_FSMC_A4: U1.20, U5.D2
PROC_FSMC_A5: U1.21, U5.A2
PROC_FSMC_A6: U1.60, U5.C2
PROC_FSMC_A7: U1.63, U5.A3
PROC_FSMC_A8: U1.64, U5.B3
PROC_FSMC_A9: U1.65, U5.C3
PROC_FSMC_A10: U1.66, U5.D3
PROC_FSMC_A11: U1.67, U5.C4
PROC_FSMC_A12: U1.106, U5.A5
PROC_FSMC_A13: U1.107, U5.B5
PROC_FSMC_A14: U1.108, U5.C5
PROC_FSMC_A15: U1.109, U5.D7
PROC_FSMC_A16: U1.99, U5.D8
PROC_FSMC_A17: U1.100, U5.A7
PROC_FSMC_A18: U1.101, U5.B7
PROC_FSMC_CLK: U1.145, U5.E6
PROC_FSMC_NE4: R17.1, U5.B4
PROC_FSMC_NL: R16.1, U1.165, U5.F6
PROC_FSMC_NOE: R18.1, U1.146, U5.F8
PROC_FSMC_NWAIT: U1.150, U5.F7
PROC_FSMC_NWE: R20.1, U1.147, U5.G8
VCC_S1_13V7: C37.1, C40.1, C41.1, J1.1, R21.2, U9.4
VCC_TIER1_3V3: C1.1, C2.1, C3.1, C4.1, C5.1, C6.1, C7.1, C8.1, C9.1, C10.1, C11.1, C12.1, C13.1, C14.1, C15.1, C16.1, C17.1, C18.1, C25.1, C26.1, C27.1, C28.1, C29.1, C30.1, C31.1, C34.1, C35.1, C38.1, C39.1, C42.1, C43.1, C44.1, F1.2, R4.2, R5.2, R6.2, R7.2, R8.2, R9.2, R10.2, R13.2, R16.2, R17.2, R18.2, R19.2, R20.2, R22.1, R24.2, R25.2, R27.1, U1.6, U1.15, U1.23, U1.36, U1.49, U1.62, U1.72, U1.82, U1.91, U1.103, U1.114, U1.127, U1.136, U1.149, U1.159, U1.172, U2.1, U3.8, U4.8, U5.A6, U5.D5, U5.D6, U5.G4, U5.H3, U7.4, U8.1, U8.2, U9.5, U10.6, U13.5, U14.5, U15.5

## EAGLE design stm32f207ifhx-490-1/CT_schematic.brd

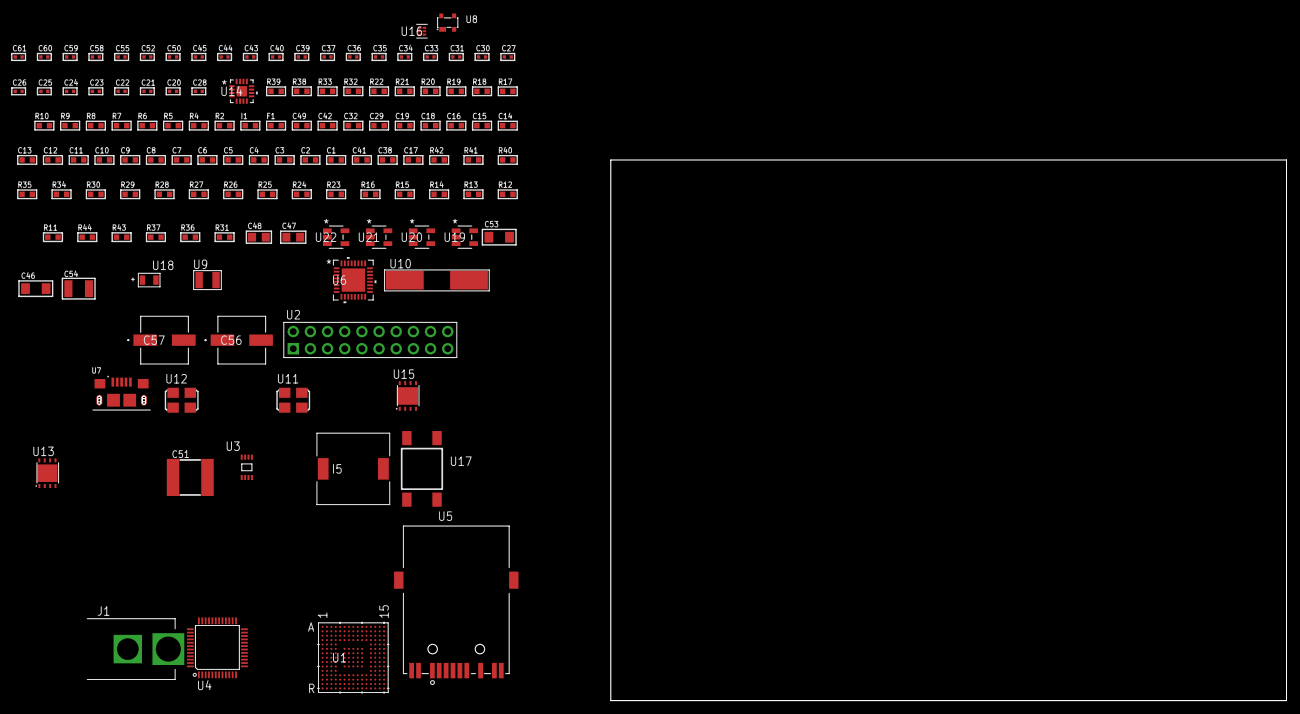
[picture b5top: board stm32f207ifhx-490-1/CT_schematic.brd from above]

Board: 2 copper layers, 129 parts (0 on the bottom side), 83 nets, no tracks yet.

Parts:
C1, C19, C29, C32, C42, C49: 1e-06; C0603
C2, C3, C4, C5, C6, C7, C8, C9, C10, C11, C12, C13, C14, C15, C16: 1e-07; C0603
C17: 4.7e-06; C0603
C18: 1e-08; C0603
C20, C21, C26, C30, C33, C35, C36, C37, C39, C40, C50, C55: 1e-07; C0402
C22, C23, C24, C25: 1e-11; C0402
C27, C31, C34, C43, C44, C45, C52, C58, C59, C60, C61: 1e-08; C0402
C28: 2.2e-08; C0402
C38, C41: 2.2e-06; C0603
C46, C53: 1e-05; C1206
C47, C48: 1e-05; C0805
C51: 6.8e-05; 2220
C54: 1e-05; C1210
C56, C57: 0.0001; EXV-9H
F1: 240.0; L0603
I1: 97.0; R0603
I5: 3.8e-06; DR1040
J1: PJ-037B; PJ-037B_PACKAGE
R2, R33, R39: 1000.0; R0603
R4, R5, R6, R22: 4700.0; R0603
R7, R8, R9, R10: 2200.0; R0603
R11, R12, R13, R14, R15, R16, R23, R24, R25, R26, R27, R28, R29, R30, R40, R41: 10000.0; R0603
R17, R18: 0.1; R0603
R19, R20, R32: 200.0; R0603
R21: 2490.0; R0603
R31, R37: 100000.0; R0603
R34: 20000.0; R0603
R35: 39000.0; R0603
R36, R43: 300000.0; R0603
R38: 2231.0; R0603
R42: 82000.0; R0603
R44: 120000.0; R0603
U1: STM32F207IFH6; UFBGA176_25
U2: TST-110-05-T-D-RA
U3: 24AA64T-I/MNY; TDFN-8/6MM
U4: RTL8201FL-VB-CG
U5: 7498011122R
U6: TUSB1210BRHBR; RHB32_3P45X3P45
U7: 10118193-0001LF; FCI_10118193-0001LF
U8: prtr5v0u2ax; SOT143B
U9: ABS07-32.768KHZ-7-T
U10: ABLS-25.000MHZ-B2F-T
U11: ASFL1-25MHZ-NCS; ASFL1
U12: ASFL1-26MHZ-NCS; ASFL1
U13, U15: LP3878SDX-ADJ/NOPB; WSON-8
U14: LTC3601EUD#PBF; QFN-16_EP
U16: TPS3895ADRYR; SON-6
U17: 4-1437565-2; SW_4-1437565-2
U18: Q65110A2395; LGM67K-G1J2-24-Z
U19, U20, U21, U22: nc7sz125m5x; NC7SZ125M5X

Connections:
CLK_CRYSTAL_U1_E1: C22.1, U1.E1, U9.1
CLK_CRYSTAL_U1_F1: C23.1, U1.F1, U9.2
CLK_CRYSTAL_U1_G1: C24.1, U1.G1, U10.1
CLK_CRYSTAL_U1_H1: C25.1, U1.H1, U10.2
CLK_U4_43: U4.43, U11.3
CLK_U6_1: U6.1, U12.3
GND: C1.2, C2.2, C3.2, C4.2, C5.2, C6.2, C7.2, C8.2, C9.2, C10.2, C11.2, C12.2, C13.2, C14.2, C15.2, C16.2, C17.2, C18.2, C19.2, C20.2, C21.2, C22.2, C23.2, C24.2, C25.2, C26.2, C27.2, C28.2, C29.2, C30.2, C31.2, C32.2, C33.2, C34.2, C35.2, C36.2, C37.2, C38.2, C39.2, C40.2, C41.2, C42.2, C43.2, C44.2, C45.2, C46.2, C47.2, C48.2, C49.2, C51.1, C51.2, C52.2, C53.2, C54.2, C55.2, C56.2, C57.2, C58.2, C59.2, C60.2, C61.2, J1.2, R2.2, R11.2, R14.2, R16.2, R17.2, R18.2, R21.2, R23.2, R24.2, R26.2, R33.2, R34.2, R36.2, R39.2, R42.2, R44.2, U1.D5, U1.D7, U1.D8, U1.D9, U1.F2, U1.F6, U1.F7, U1.F8, U1.F9, U1.F10, U1.F12, U1.G2, U1.G6, U1.G7, U1.G8, U1.G9, U1.G10, U1.G12, U1.H6, U1.H7, U1.H8, U1.H9, U1.H10, U1.H12, U1.J6, U1.J7, U1.J8, U1.J9, U1.J10, U1.K6, U1.K7, U1.K8, U1.K9, U1.K10, U1.M1, U1.M8, U1.M9, U1.N1, U2.4, U2.6, U2.8, U2.10, U2.12, U2.14, U2.16, U2.18, U2.20, U3.4, U3.7, U4.7, U4.20, U4.33, U4.42, U4.47, U5.9, U6.33, U7.5, U7.6, U7.7, U7.8, U7.9, U8.1, U11.2, U12.2, U13.3, U13.PAD, U14.1, U14.9, U14.17, U15.3, U15.PAD, U16.2, U18.C, U19.2, U19.3, U20.1, U20.3, U21.1, U21.3, U22.1, U22.3
NET_U1_A5: R7.1, U1.A5, U3.6
NET_U1_B4: R8.1, U1.B4, U3.5
NET_U1_D6: R11.1, U1.D6
NET_U1_F13: C21.1, U1.F13
NET_U1_J1: R5.1, U1.J1, U21.4
NET_U1_L4: R12.1, U1.L4
NET_U1_R1: C18.1, C19.1, F1.1, U1.P1, U1.R1
NET_U1_R15: U17.3, U17.4
NET_U3_1: R14.1, U3.1
NET_U3_2: R15.1, U3.2
NET_U3_3: R16.1, U3.3
NET_U4_6: C29.1, C30.1, C31.1, I1.1, U4.6, U4.41
NET_U4_10: R26.1, U4.10
NET_U4_13: R23.1, U4.13
NET_U4_18: R27.1, U4.18
NET_U4_29: R4.1, U4.29, U20.4
NET_U4_32: R22.1, U4.32
NET_U4_34: R24.1, U4.34
NET_U4_35: R25.1, U4.35
NET_U4_39: R28.1, U4.39
NET_U4_40: C36.1, U4.40
NET_U4_46: R21.1, U4.46
NET_U4_48: C35.1, U4.48
NET_U5_1: U4.1, U5.1
NET_U5_3: U4.2, U5.3
NET_U5_4: U4.4, U5.4
NET_U5_5: C28.1, U5.2, U5.5
NET_U5_6: U4.5, U5.6
NET_U5_8: R18.1, U5.8
NET_U5_10: R19.1, U5.10
NET_U5_12: R20.1, U5.12
NET_U5_13: R17.1, U5.13, U5.14
NET_U6_11: R29.1, U6.11
NET_U6_12: C41.1, U6.12
NET_U6_14: R30.1, U6.14
NET_U6_20: C38.1, U6.20
NET_U6_27: R6.1, U6.27, U22.4
NET_U7_1: C42.1, U6.22, U7.1, U8.4
NET_U7_2: U6.19, U7.2, U8.3
NET_U7_3: U6.18, U7.3, U8.2
NET_U13_1: C45.1, U13.1
NET_U13_6: R32.2, R33.1, U13.6
NET_U13_8: R31.1, U13.8
NET_U14_3: C50.2, I5.1, U14.3, U14.4
NET_U14_6: C50.1, U14.6
NET_U14_7: C49.1, U14.7, U14.12
NET_U14_10: R36.1, U14.10
NET_U14_11: R34.1, R35.1, U14.11
NET_U14_ATNET_3: I5.2, R35.2
NET_U15_1: C52.1, U15.1
NET_U15_6: R38.2, R39.1, U15.6
NET_U15_8: R37.1, U15.8
NET_U16_1: R41.1, R42.1, U16.1
NET_U16_3: R43.2, R44.1, U16.3
NET_U16_4: R40.1, U16.4, U19.4, U20.2, U21.2, U22.2
NET_U17_1: R2.1, U17.1, U17.2
PROC_SYS_JTCK_SWCLK: U1.A14, U2.9
PROC_SYS_JTDO_SWO: U1.A10, U2.13
PROC_SYS_JTMS_SWDIO: U1.A15, U2.7
PROC_USB_OTG_HS_ULPI_CK: U1.P4, U6.26
PROC_USB_OTG_HS_ULPI_D0: U1.R2, U6.3
PROC_USB_OTG_HS_ULPI_D1: U1.R5, U6.4
PROC_USB_OTG_HS_ULPI_D2: U1.R4, U6.5
PROC_USB_OTG_HS_ULPI_D3: U1.R12, U6.6
PROC_USB_OTG_HS_ULPI_D4: U1.R13, U6.7
PROC_USB_OTG_HS_ULPI_D5: U1.P12, U6.9
PROC_USB_OTG_HS_ULPI_D6: U1.P13, U6.10
PROC_USB_OTG_HS_ULPI_D7: U1.A6, U6.13
PROC_USB_OTG_HS_ULPI_DIR: U1.E4, U6.31
PROC_USB_OTG_HS_ULPI_NXT: U1.H4, U6.2
PROC_USB_OTG_HS_ULPI_STP: U1.M2, U6.29
RST_OUT_U2_SRESET_B: R13.1, U2.15, U19.1
VCC_S1_9V8: C46.1, C48.1, C53.1, C56.1, C57.1, J1.1, R31.2, R37.2, U13.4, U14.15, U14.16, U15.4
VCC_TIER1_1V2: C20.1, C47.1, R32.1, U1.M10, U13.5
VCC_TIER1_1V8: C1.1, C2.1, C3.1, C4.1, C5.1, C6.1, C7.1, C8.1, C9.1, C10.1, C11.1, C12.1, C13.1, C14.1, C15.1, C16.1, C17.1, C26.1, C27.1, C39.1, C40.1, C51.2, C55.1, C58.1, C59.1, C60.1, C61.1, F1.2, I5.2, R5.2, R6.2, R7.2, R8.2, R9.2, R10.2, R12.2, R13.2, R15.2, R29.2, R30.2, R35.2, R40.2, R41.2, R43.1, U1.C1, U1.C5, U1.C7, U1.C8, U1.C9, U1.F3, U1.G3, U1.G13, U1.H13, U1.J12, U1.J13, U1.K4, U1.N8, U1.N9, U1.N10, U2.1, U3.8, U6.28, U6.30, U6.32, U14.8, U16.6, U19.5, U20.5, U21.5, U22.5
VCC_TIER1_3V3: C32.1, C33.1, C34.1, C37.1, C43.1, C44.1, C54.1, I1.2, R4.2, R22.2, R25.2, R27.2, R28.2, R38.1, U4.15, U4.21, U4.37, U6.21, U11.4, U12.4, U15.5
